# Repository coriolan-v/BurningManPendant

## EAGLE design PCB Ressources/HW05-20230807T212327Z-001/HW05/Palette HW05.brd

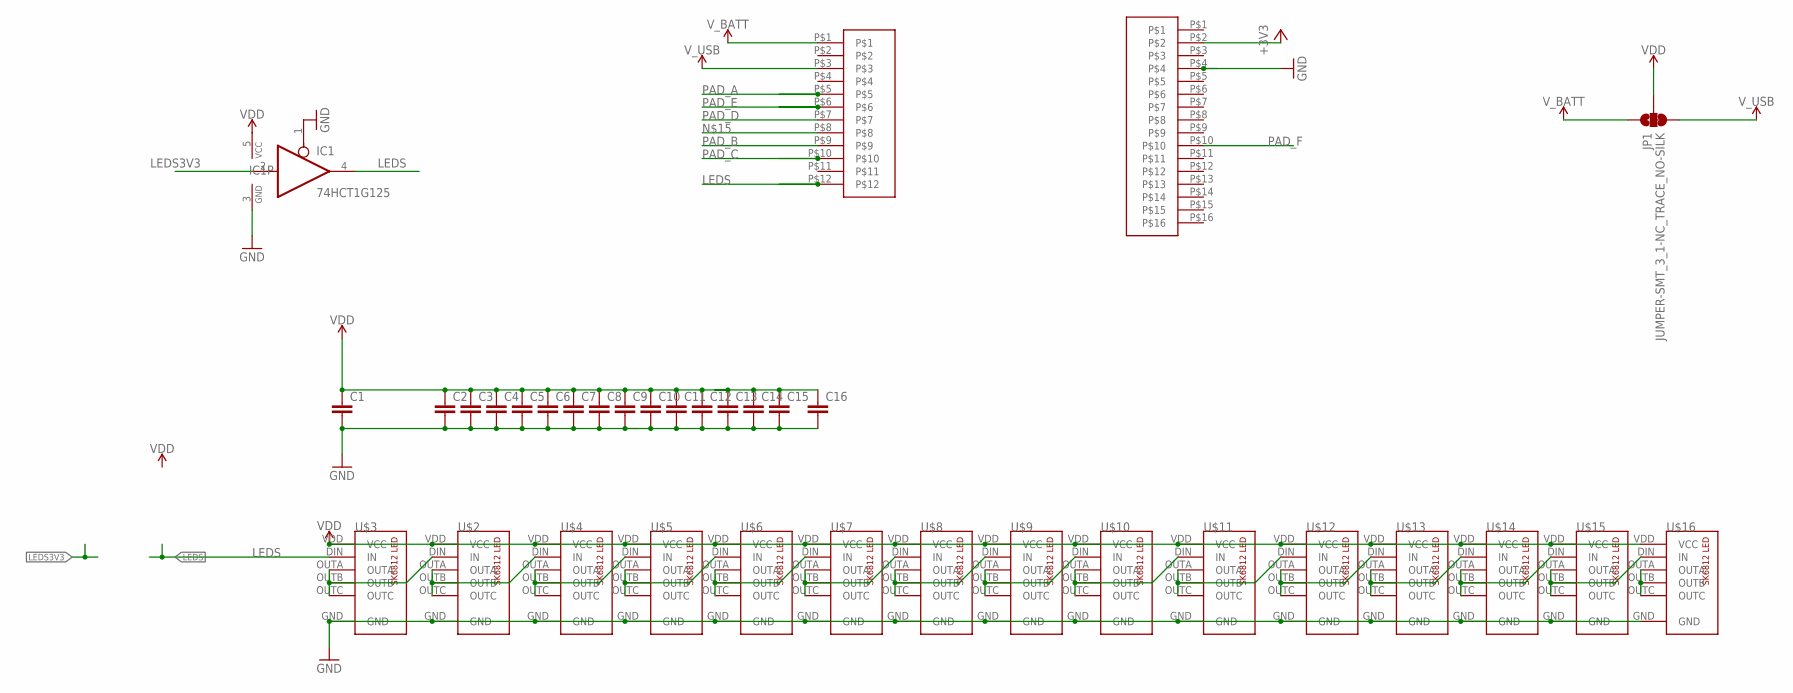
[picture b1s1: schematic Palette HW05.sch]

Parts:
C1, C2, C3, C4, C5, C6, C7, C8, C9, C10, C11, C12, C13, C14, C15: C-EUC0402K; C0402K
C16: C-EUC0805K; C0805K
IC1: 74HCT1G125; SOT23-5
JP1: JUMPER-SMT_3_1-NC_TRACE_NO-SILK; SMT-JUMPER_3_1-NC_TRACE_NO-SILK
U$2, U$3, U$4, U$5, U$6, U$7, U$8, U$9, U$10, U$11, U$12, U$13, U$14, U$15, U$16: SK6812OK; SK6812_V2C
U$17: SMD-FEMALE-HEADER-16
U$18: SMD-FEMALE-HEADER-12

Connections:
+3V3: U$17.P$2
GND: C1.2, C2.2, C3.2, C4.2, C5.2, C6.2, C7.2, C8.2, C9.2, C10.2, C11.2, C12.2, C13.2, C14.2, C15.2, C16.2, IC1.1 (OE), IC1.3 (GND), U$2.GND, U$3.GND, U$4.GND, U$5.GND, U$6.GND, U$7.GND, U$8.GND, U$9.GND, U$10.GND, U$11.GND, U$12.GND, U$13.GND, U$14.GND, U$15.GND, U$16.GND, U$17.P$4
LEDS: IC1.4 (O), U$3.DIN (IN), U$18.P$12
LEDS3V3: IC1.2 (I)
unnamed: U$2.DIN (IN), U$3.OUTA, U$3.OUTB, U$3.OUTC
unnamed: U$2.OUTA, U$2.OUTB, U$2.OUTC, U$4.DIN (IN)
unnamed: U$4.OUTA, U$4.OUTB, U$4.OUTC, U$5.DIN (IN)
unnamed: U$5.OUTA, U$5.OUTB, U$5.OUTC, U$6.DIN (IN)
unnamed: U$6.OUTA, U$6.OUTB, U$6.OUTC, U$7.DIN (IN)
unnamed: U$7.OUTA, U$7.OUTB, U$7.OUTC, U$8.DIN (IN)
unnamed: U$8.OUTA, U$8.OUTB, U$8.OUTC, U$9.DIN (IN)
unnamed: U$9.OUTA, U$9.OUTB, U$9.OUTC, U$10.DIN (IN)
unnamed: U$10.OUTA, U$10.OUTB, U$10.OUTC, U$11.DIN (IN)
unnamed: U$11.OUTA, U$11.OUTB, U$11.OUTC, U$12.DIN (IN)
unnamed: U$12.OUTA, U$12.OUTB, U$12.OUTC, U$13.DIN (IN)
unnamed: U$13.OUTA, U$13.OUTB, U$13.OUTC, U$14.DIN (IN)
unnamed: U$14.OUTA, U$14.OUTB, U$14.OUTC, U$15.DIN (IN)
unnamed: U$15.OUTA, U$15.OUTB, U$15.OUTC, U$16.DIN (IN)
unnamed: U$16.OUTA, U$16.OUTB, U$16.OUTC
PAD_A: U$18.P$5
PAD_B: U$18.P$9
PAD_C: U$18.P$10
PAD_D: U$18.P$7
PAD_E: U$18.P$6
PAD_F: U$17.P$10
VDD: C1.1, C2.1, C3.1, C4.1, C5.1, C6.1, C7.1, C8.1, C9.1, C10.1, C11.1, C12.1, C13.1, C14.1, C15.1, C16.1, IC1.5 (VCC), JP1.2, U$2.VDD (VCC), U$3.VDD (VCC), U$4.VDD (VCC), U$5.VDD (VCC), U$6.VDD (VCC), U$7.VDD (VCC), U$8.VDD (VCC), U$9.VDD (VCC), U$10.VDD (VCC), U$11.VDD (VCC), U$12.VDD (VCC), U$13.VDD (VCC), U$14.VDD (VCC), U$15.VDD (VCC), U$16.VDD (VCC)
V_BATT: JP1.1, U$18.P$1
V_USB: JP1.3, U$18.P$3

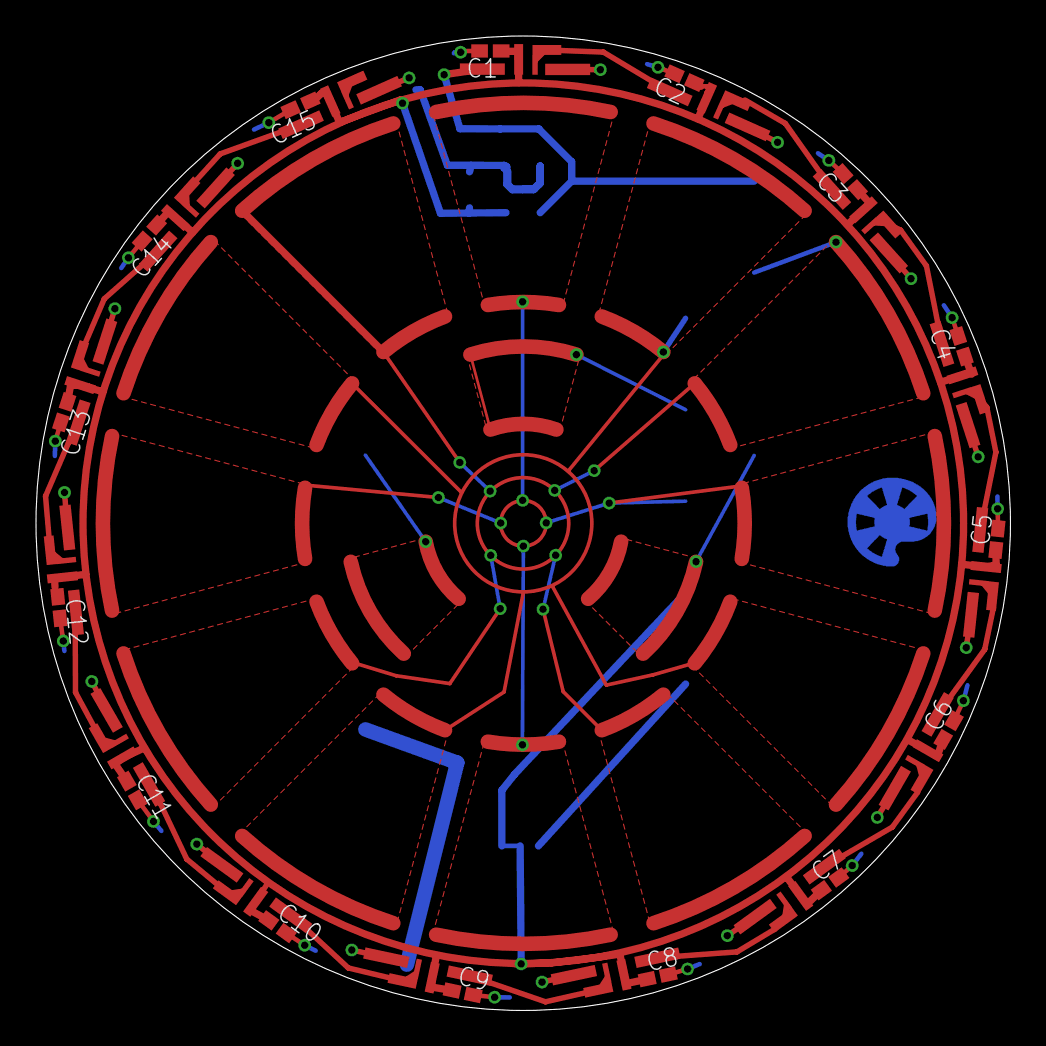
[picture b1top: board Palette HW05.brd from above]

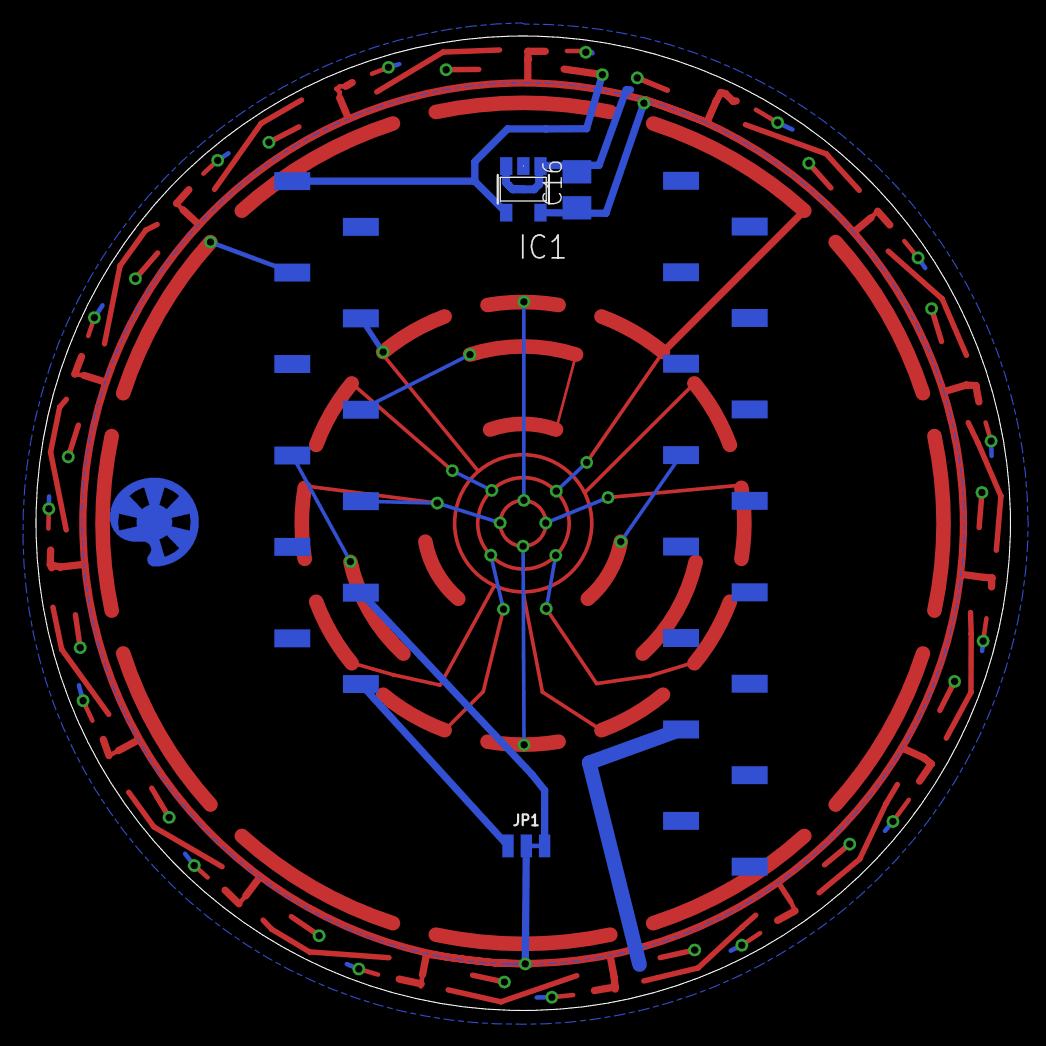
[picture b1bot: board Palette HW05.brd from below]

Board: 2 copper layers, 54.1 x 54.1 mm, 35 parts (5 on the bottom side), 20 nets.

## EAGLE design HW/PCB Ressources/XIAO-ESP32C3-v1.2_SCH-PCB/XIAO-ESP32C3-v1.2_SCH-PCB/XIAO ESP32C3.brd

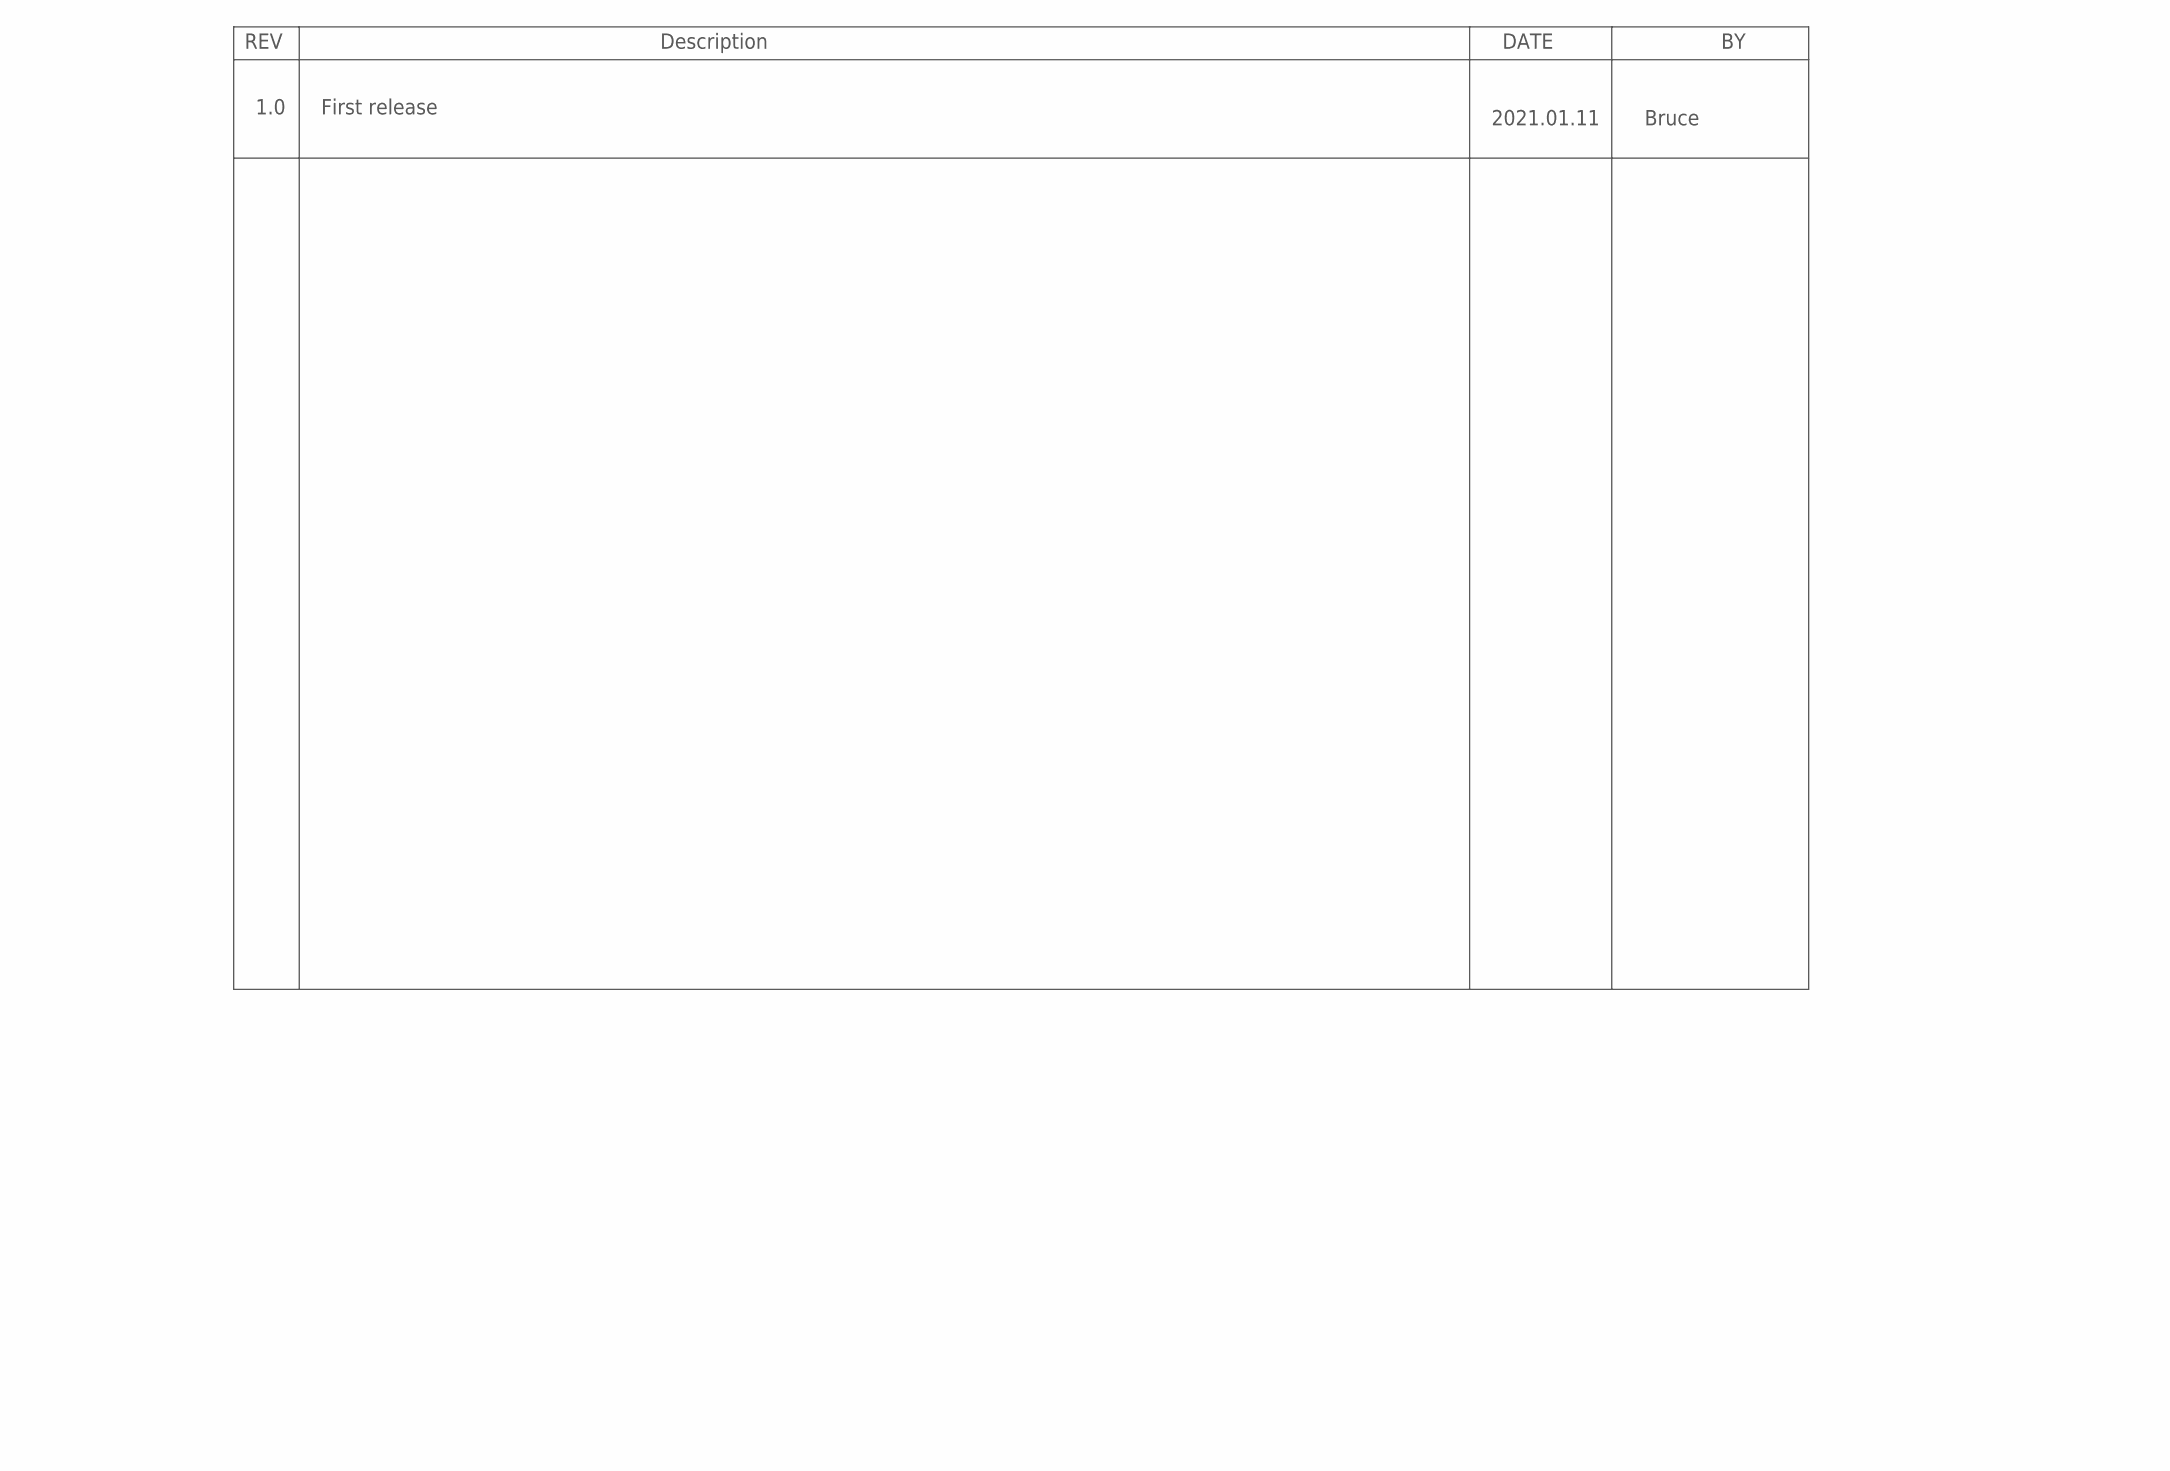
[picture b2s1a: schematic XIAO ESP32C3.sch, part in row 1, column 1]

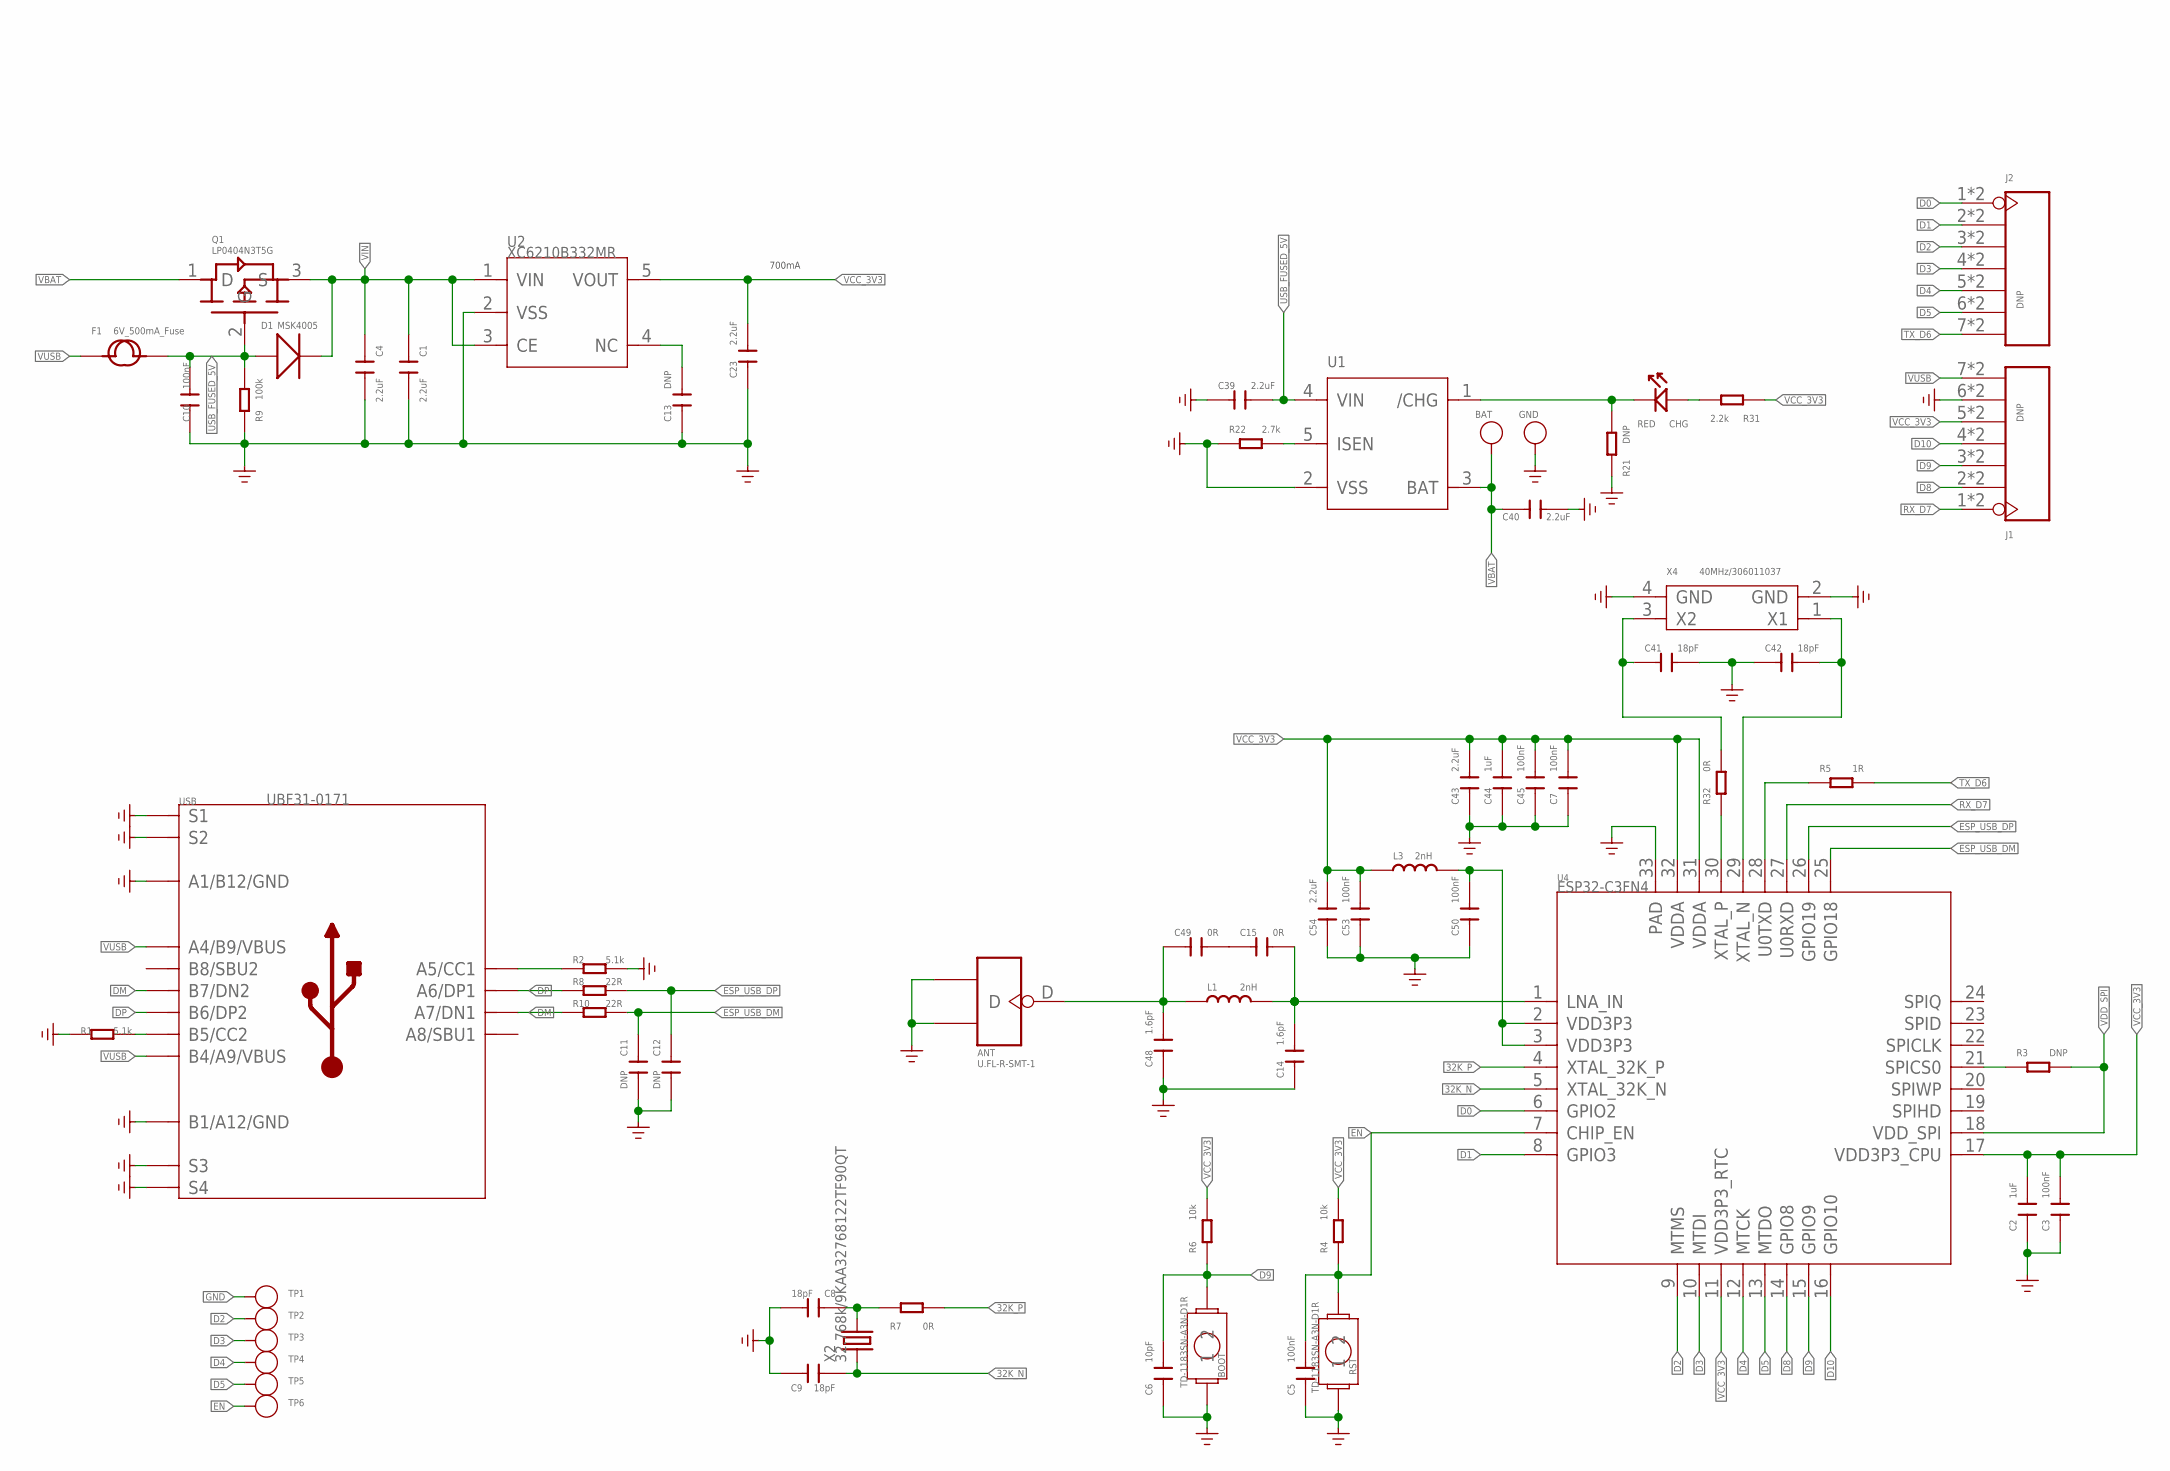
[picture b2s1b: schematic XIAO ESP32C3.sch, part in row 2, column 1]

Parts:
ANT: U.FL-R-SMT-1; U-FL3P-SMD-2.6X2.6X1.0MM
BAT: DNP; TP-80X40MIL
BOOT: TD-1183SN-A3N-D1R; BUTTON_TD1183SA
C1, C4, C23, C39, C40, C43, C54: 2.2uF; C0201
C2, C44: 1uF; C0201
C3, C5, C7, C10, C45, C50, C53: 100nF; C0201
C6: 10pF; C0201
C8, C9, C41, C42: 18pF; C0201
C11, C12, C13: DNP; C0201
C14, C48: 1.6pF; C0201
C15, C49: 0R; C0201
CHG: RED; LED-0402
D1: MSK4005; SOD-523
F1: 6V_500mA_Fuse; F0603
GND: DNP; TP-80X40MIL
J1, J2: DNP; H7-HALF-HOLE-2.54
L1, L3: 2nH; L0201
Q1: LP0404N3T5G; PMOS_1.0*0.6*0.35MM
R1, R2: 5.1k; R0201
R3, R21: DNP; R0201
R4, R6: 10k; R0201
R5: 1R; R0201
R7, R32: 0R; R0201
R8, R10: 22R; R0201
R9: 100k; R0201
R22: 2.7k; R0201
R31: 2.2k; R0201
RST: TD-1183SN-A3N-D1R; BUTTON_TD1183SA
TP1, TP2, TP3, TP4, TP5, TP6: DNP; TP-D45MIL
U1: PMIC-XC6802MR; SOT-25
U2: XC6210B332MR; SOT-25
U4: ESP32-C3FN4; QFN32G-0.5-5X5MM
USB: UBF31-0171; USB2.0-TYPE-C
X2: 32.768k/9KAA32768122TF90QT; X2-SMD-1.6X1.0X0.5MM
X4: 40MHz/306011037; X4-SMD-2.0X1.6X0.5MM

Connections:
32K_N: C9.1, U4.5 (XTAL_32K_N), X2.1
32K_P: R7.1, U4.4 (XTAL_32K_P)
!CHG: CHG.-, R21.1, U1.1 (/CHG)
D0: J2.1, J2.13 (1), U4.6 (GPIO2)
D1: J2.2, J2.14 (2), U4.8 (GPIO3)
D2: J2.3, J2.15 (3), TP2.T, U4.9 (MTMS)
D3: J2.4, J2.16 (4), TP3.T, U4.10 (MTDI)
D4: J2.5, J2.17 (5), TP4.T, U4.12 (MTCK)
D5: J2.6, J2.18 (6), TP5.T, U4.13 (MTDO)
D8: J1.2, J1.14 (2), U4.14 (GPIO8)
D9: BOOT.2, C6.2, J1.3, J1.15 (3), R6.1, U4.15 (GPIO9)
D10: J1.4, J1.16 (4), U4.16 (GPIO10)
DM: R10.1, USB.A7 (A7/DN1), USB.B7 (B7/DN2)
DP: R8.1, USB.A6 (A6/DP1), USB.B6 (B6/DP2)
EN: C5.2, R4.1, RST.2, TP6.T, U4.7 (CHIP_EN)
ESP_USB_DM: C11.2, R10.2, U4.25 (GPIO18)
ESP_USB_DP: C12.2, R8.2, U4.26 (GPIO19)
GND: ANT.GND1, ANT.GND2, BOOT.1, C1.2, C2.1, C3.1, C4.2, C5.1, C6.1, C7.1, C8.2, C9.2, C10.1, C11.1, C12.1, C13.1, C14.1, C23.1, C39.1, C40.2, C41.2, C42.2, C43.1, C44.1, C45.1, C48.1, C50.1, C53.1, C54.1, GND.1, J1.6, J1.18 (6), R1.1, R2.2, R9.1, R21.2, R22.2, RST.1, TP1.T, U1.2 (VSS), U2.2 (VSS), U4.33 (PAD), USB.A1_B12 (A1/B12/GND), USB.B1_A12 (B1/A12/GND), USB.S1, USB.S2, USB.S3, USB.S4, USB.S5 (S1), USB.S6 (S2), X4.2 (GND), X4.4 (GND)
unnamed: R2.1, USB.A5 (A5/CC1)
unnamed: R1.2, USB.B5 (B5/CC2)
unnamed: R3.1, U4.21 (SPICS0)
unnamed: C8.1, R7.2, X2.2
unnamed: C13.2, U2.4 (NC)
unnamed: C15.2, C49.1
unnamed: R22.1, U1.5 (ISEN)
unnamed: CHG.+, R31.2
unnamed: C14.2, C15.1, L1.2, U4.1 (LNA_IN)
unnamed: C41.1, R32.2, X4.3 (X2)
unnamed: C42.1, U4.29 (XTAL_N), X4.1 (X1)
unnamed: ANT.D, C48.2, C49.2, L1.1
unnamed: R5.2, U4.28 (U0TXD)
unnamed: C50.2, L3.2, U4.2 (VDD3P3), U4.3 (VDD3P3)
unnamed: R32.1, U4.30 (XTAL_P)
RX_D7: J1.1, J1.13 (1), U4.27 (U0RXD)
TX_D6: J2.7, J2.19 (7), R5.1
USB_FUSED_5V: C10.2, C39.2, D1.+, F1.2, Q1.2 (G), R9.2, U1.4 (VIN)
VBAT: BAT.1, C40.1, Q1.1 (D), U1.3 (BAT)
VCC_3V3: C2.2, C3.2, C7.2, C23.2, C43.2, C44.2, C45.2, C53.2, C54.2, J1.5, J1.17 (5), L3.1, R4.2, R6.2, R31.1, U2.5 (VOUT), U4.11 (VDD3P3_RTC), U4.17 (VDD3P3_CPU), U4.31 (VDDA), U4.32 (VDDA)
VDD_SPI: R3.2, U4.18 (VDD_SPI)
VIN: C1.1, C4.1, D1.-, Q1.3 (S), U2.1 (VIN), U2.3 (CE)
VUSB: F1.1, J1.7, J1.19 (7), USB.A4_B9 (A4/B9/VBUS), USB.B4_A9 (B4/A9/VBUS)

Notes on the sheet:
1.0
First release
2021.01.11
Bruce
700mA

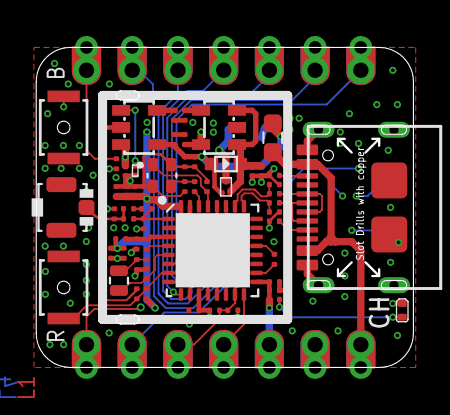
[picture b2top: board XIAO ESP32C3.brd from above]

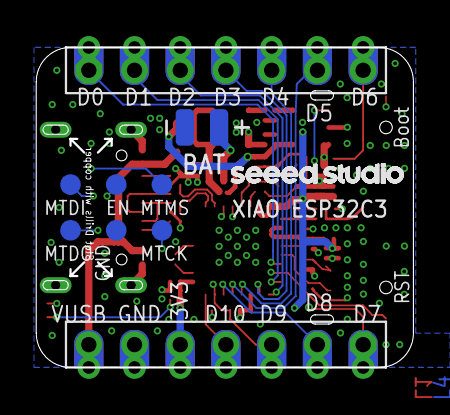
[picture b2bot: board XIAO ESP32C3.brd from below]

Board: 4 copper layers, 21.0 x 17.8 mm, 68 parts (9 on the bottom side), 41 nets.

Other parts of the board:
U$2: LOGO-SEEED-NEW-1X9.6MM

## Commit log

2023-08-02 added illustrator
2023-08-02 added PCB
2023-08-02 added dxf
2023-08-02 updte jpg
2023-08-02 added fonts
2023-08-02 updates on the pcb and fw
2023-08-03 Added server code for BurnerFinder
2023-08-06 Working on FW and PCB
2023-08-07 Progress on PCBs
2023-08-07 Clean
2023-08-08 added brc map
2023-08-08 added Qr codes
2023-08-08 progress on pcb
2023-08-09 working on Finder FW
2023-08-10 Final PCB
2023-08-16 Side and backplate PCB, Rhino
2023-08-18 sleep and LED
2023-08-18 FW dev LED BLE scan
2023-08-19 work on low power
2023-10-08 added FW test LED, nrf52840
2023-11-12 testing leds
2023-11-14 new code without delay
2024-03-24 working on AI and PCB
2024-03-24 update AI
2024-03-27 working on PCB
2024-03-27 update all PCBs
2024-03-28 added Nowhere PCB
2024-03-28 renamed
2024-03-28 gerbers
2024-03-31 finished PCB
2024-03-31 added ref image
2024-04-01 Organise repos
2024-04-04 added saucer AI file
2024-04-04 finished nest pcb
2024-06-02 working on nowhere pcb
2024-06-06 pcb update
2024-06-12 final update
2024-06-14 final rev
2024-06-15 new rev

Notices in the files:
parts and their libraries:
SparkFun-Jumpers: Licensing: Creative Commons ShareAlike 4.0 International - https://creativecommons.org/licenses/by-sa/4.0
